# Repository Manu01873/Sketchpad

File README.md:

# Sketchpad
The Hackpad is a compact macro pad designed to streamline 3D modeling workflows and daily tasks. The project runs on the Seeed Studio XIAO RP2040 microcontroller and utilizes KMK Firmware built on top of CircuitPython.

The main feature of this setup is the rotary encoder logic. Instead of dedicating a physical key to switch layers, clicking the encoder freezes normal inputs and turns the knob into a manual layer selector. The user rotates the encoder to cycle through available layers on the OLED screen and clicks it again to confirm the selection.

## Key Features

* 3 independent layers (Multimedia, Cad Modeling, and Productivity).
* Encoder-based layer navigation system, saving physical buttons for actual shortcuts.
* 0.91-inch OLED display providing immediate visual feedback of the active mode.
* Open-source code using KMK, allowing quick modifications without needing to compile firmware.

## PCB Design

The custom PCB was developed using KiCad. It utilizes direct routing to the XIAO breakout pins to avoid the necessity of a diode matrix for this layout footprint. The keyswitch footprints use the standard MX_V2 specifications, allowing compatibility with most mechanical switches. 

The custom decorative silkscreen on the board layout was designed externally and imported directly from a Figma image export.

* Layer Configuration (Keymap)
  
Layer 1: General / Multimedia
Focused on navigation and media control for daily OS use.
Button 1: Mute
Button 2: Previous track
Button 3: Next track
Encoder: Global volume control

Layer 2: Fusion 360 & 3D Sketching
Shortcuts mapped specifically for 3D modeling workflows.
Button 1: 3D Orbit (Shift + F)
Button 2: Shortcut S (Fusion command search menu)
Button 3: Shortcut E (Extrude)
Encoder: Zoom In / Zoom Out (Mouse scroll)

Layer 3: Productivity / Editing
Quick actions for text and code editing.
Button 1: Ctrl + Z
Button 2: Ctrl + X
Button 3: Ctrl + V
Encoder: Line navigation (Arrow Up / Arrow Down)

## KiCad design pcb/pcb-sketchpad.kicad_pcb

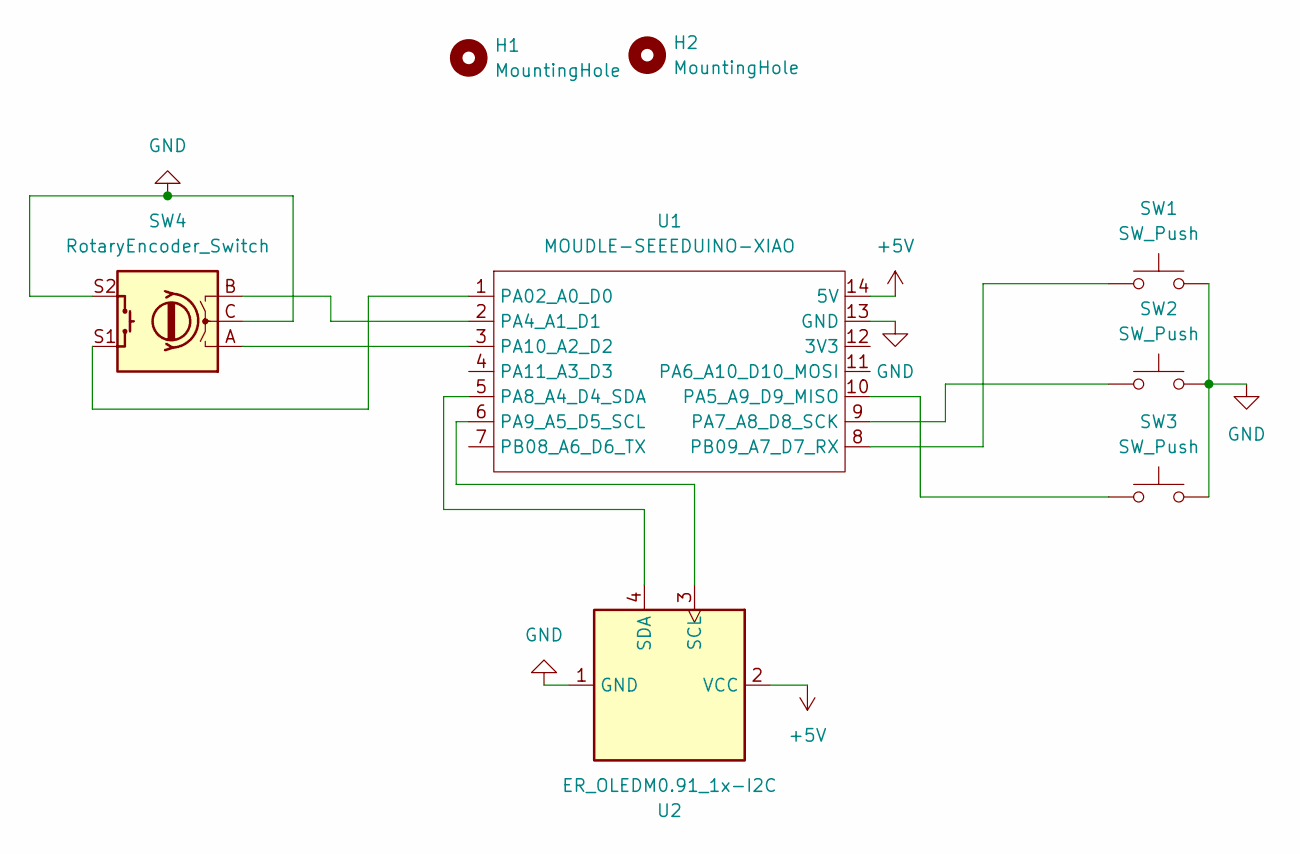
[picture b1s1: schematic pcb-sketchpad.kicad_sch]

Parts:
H1, H2: MountingHole; MountingHole_3.2mm_M3
SW1, SW2, SW3: SW_Push; SW_Cherry_MX_1.00u_PCB
SW4: RotaryEncoder_Switch; RotaryEncoder_Alps_EC11E-Switch_Vertical_H20mm
U1: MOUDLE-SEEEDUINO-XIAO; XIAO-Generic-Hybrid-14P-2.54-21X17.8MM
U2: ER_OLEDM0.91_1x-I2C

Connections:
+5V: U1.14 (5V), U2.2 (VCC)
GND: SW1.2, SW2.2, SW3.2, SW4.C, SW4.S2, U1.13 (GND), U2.1 (GND)
unnamed: SW4.S1, U1.1 (PA02_A0_D0)
unnamed: SW4.B, U1.2 (PA4_A1_D1)
unnamed: SW3.1, U1.10 (PA5_A9_D9_MISO)
unnamed: SW2.1, U1.9 (PA7_A8_D8_SCK)
unnamed: U1.5 (PA8_A4_D4_SDA), U2.4 (SDA)
unnamed: U1.6 (PA9_A5_D5_SCL), U2.3 (SCL)
unnamed: SW4.A, U1.3 (PA10_A2_D2)
unnamed: SW1.1, U1.8 (PB09_A7_D7_RX)

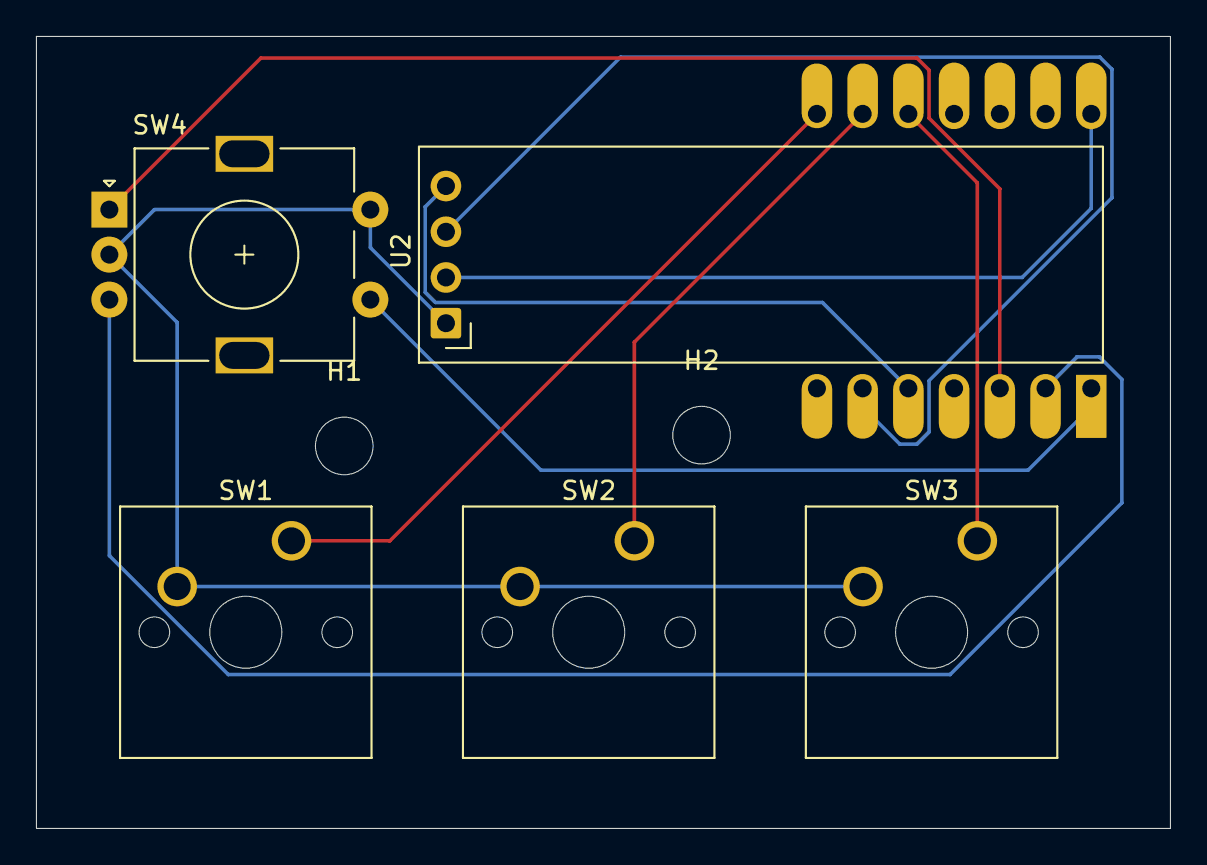
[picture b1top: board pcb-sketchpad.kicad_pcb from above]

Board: 2 copper layers, 63.0 x 44.0 mm, 8 parts (1 on the bottom side), 10 nets.

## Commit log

2026-06-12 Enhance README with project details and features
    Expanded README to include detailed project description, key features, PCB design, and layer configurations for the Hackpad.
2026-06-12 Fix image paths in README.md
    Updated image paths in README for consistency.
2026-06-12 Clean up layer configuration formatting in README
    Removed extra line breaks in layer configuration section.
